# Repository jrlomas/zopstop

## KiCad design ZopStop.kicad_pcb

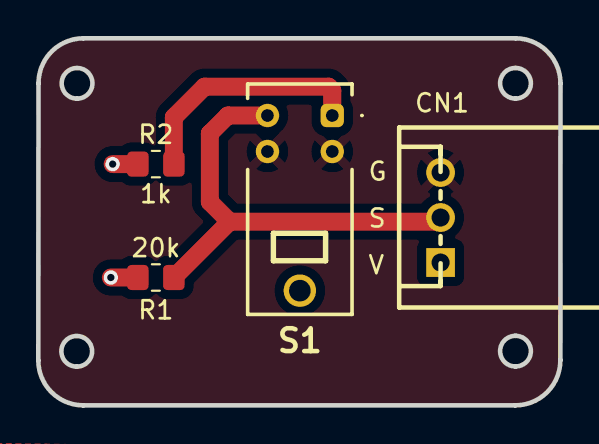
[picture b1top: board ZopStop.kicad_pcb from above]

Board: 2 copper layers, 29.0 x 20.4 mm, 4 parts (0 on the bottom side), 4 nets.

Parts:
CN1: S3B-XH-A (LF)(SN); CONN-TH_S3B-XH-A-LF-SN
R1: 20k; R_0805_2012Metric_Pad1.20x1.40mm_HandSolder
R2: 1k; R_0805_2012Metric_Pad1.20x1.40mm_HandSolder
S1: D2FP-FN2; D2FPFN2

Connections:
+5V: CN1.1, R1.2, R2.1
GND: CN1.3, S1.E1 (E), S1.K1 (K)
unnamed: R2.2, S1.A1 (A)
S: CN1.2, R1.1, S1.C1 (C)
